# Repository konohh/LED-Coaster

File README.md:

# LED-Coaster
Enlight your beverage

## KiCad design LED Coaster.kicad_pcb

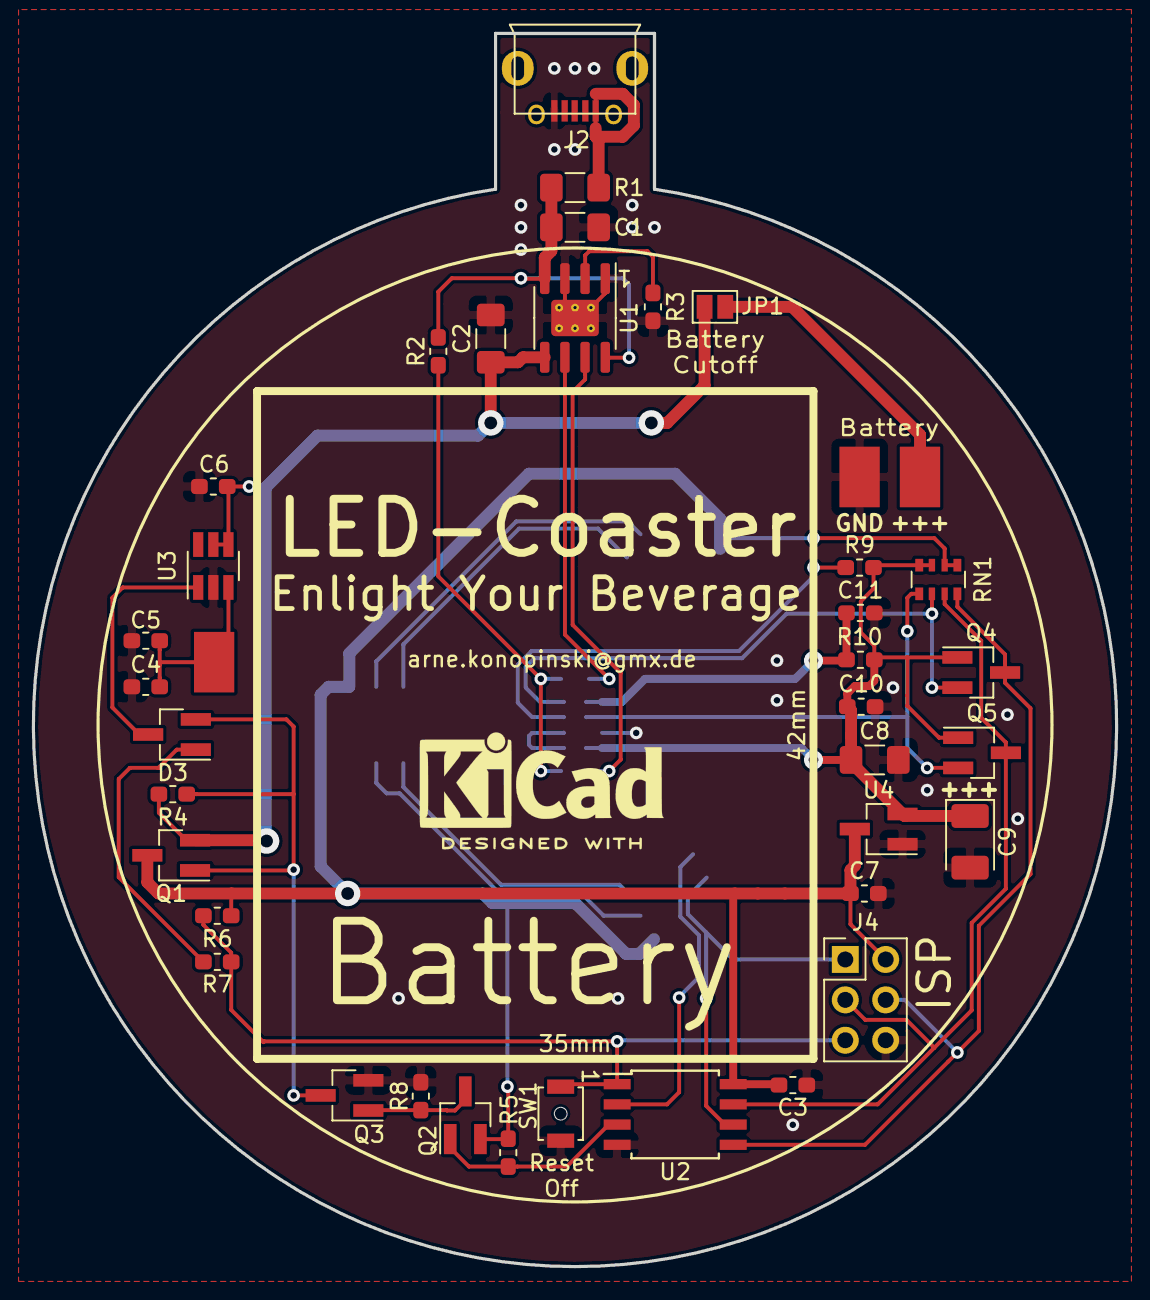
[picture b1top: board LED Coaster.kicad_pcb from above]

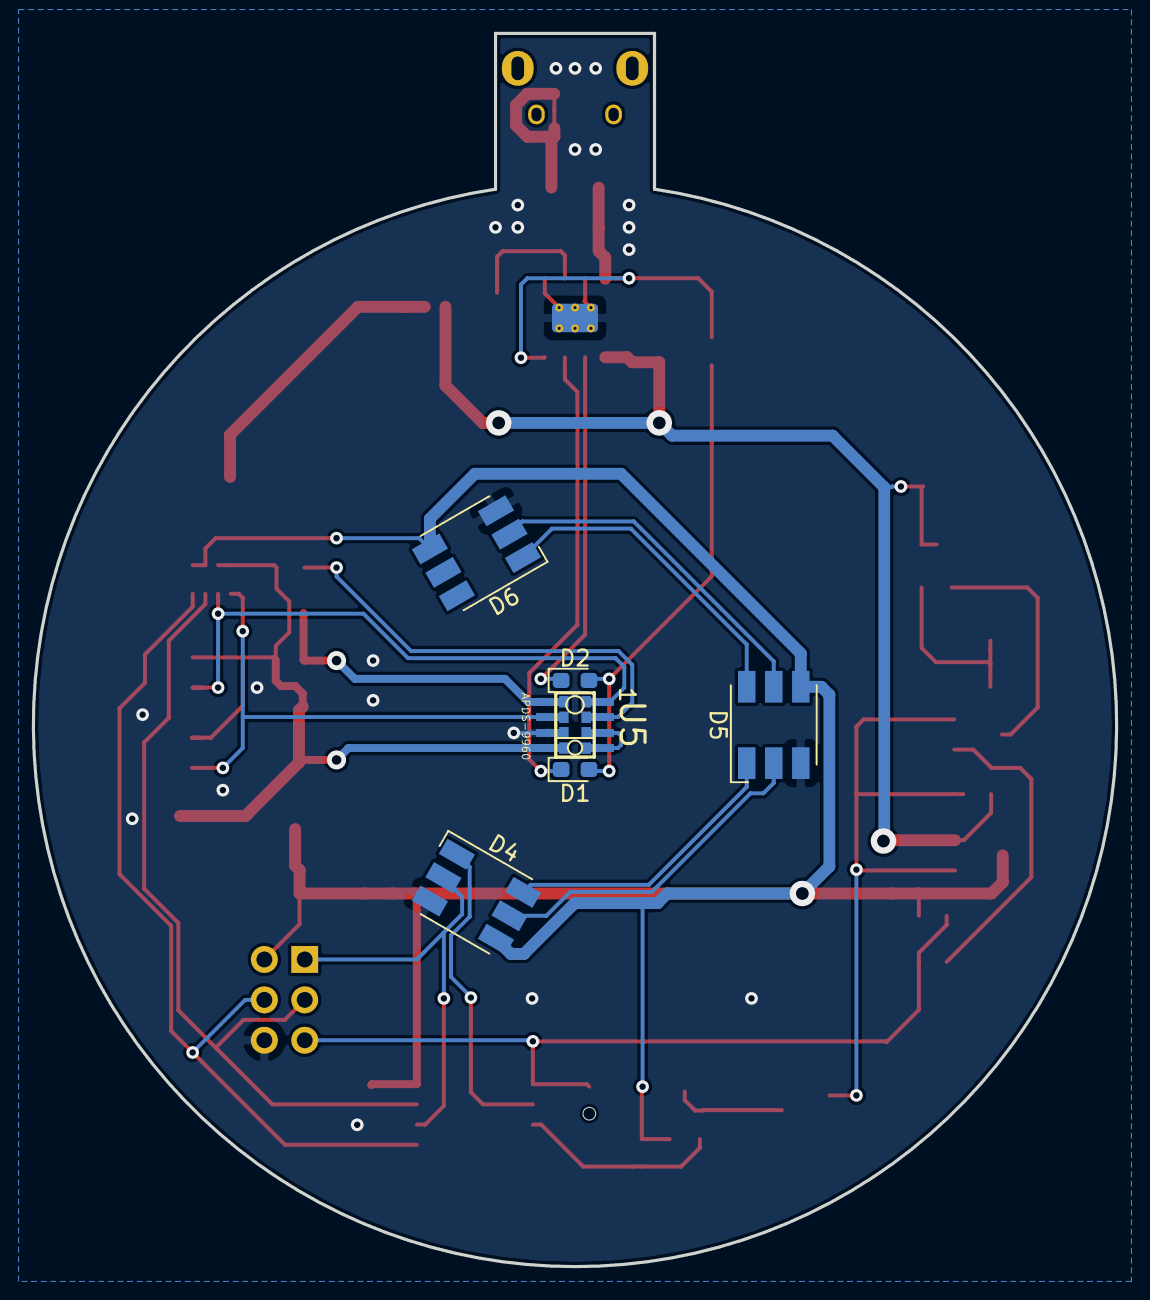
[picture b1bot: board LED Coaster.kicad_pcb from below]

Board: 2 copper layers, 68.1 x 77.6 mm, 45 parts (6 on the bottom side), 31 nets.

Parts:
C1, C2, C8: 10; C_1206_3216Metric_Pad1.42x1.75mm_HandSolder
C3, C6: .1; C_0603_1608Metric_Pad1.05x0.95mm_HandSolder
C4, C5: 33pF; C_0603_1608Metric_Pad1.05x0.95mm_HandSolder
C7, C10, C11: 1; C_0603_1608Metric_Pad1.05x0.95mm_HandSolder
C9: 47; CP_EIA-3528-15_AVX-H_Pad1.50x2.35mm_HandSolder
D1: Red; LED_0603_1608Metric_Pad1.05x0.95mm_HandSolder
D2: Green; LED_0603_1608Metric_Pad1.05x0.95mm_HandSolder
D3: BAV70; SOT-23_Handsoldering
D4, D5, D6: APA102; LED_RGB_5050-6
J1: Battery Positiv; SolderPad-100x150
J2: USB_B_Micro; USB_Micro-B_XKB_Enterprise_U254-051T-4BH23-S2B
J3: Battery GND; SolderPad-100x150
J4: ISP; PinHeader_2x03_P2.54mm_Vertical
J5: TouchPad; SolderPad-100x150
JP1: Battery Cutoff; SolderJumper-2_P1.3mm_Open_Pad1.0x1.5mm
Q1: IRLML6401; SOT-23_Handsoldering
Q2: BSS84; SOT-23_Handsoldering
Q3, Q4, Q5: BSS123; SOT-23_Handsoldering
R1: 0R4; R_1206_3216Metric_Pad1.42x1.75mm_HandSolder
R2: 1k; R_0603_1608Metric_Pad1.05x0.95mm_HandSolder
R3: 4k7; R_0603_1608Metric_Pad1.05x0.95mm_HandSolder
R4, R5, R8: 220k; R_0603_1608Metric_Pad1.05x0.95mm_HandSolder
R6: 2k2; R_0603_1608Metric_Pad1.05x0.95mm_HandSolder
R7, R9: 22k; R_0603_1608Metric_Pad1.05x0.95mm_HandSolder
R10: 22R; R_0603_1608Metric_Pad1.05x0.95mm_HandSolder
RN1: 4x10k; R_Array_Convex_4x0603
SW1: Reset / OFF; SW_SPST_B3U-1000P-B
U1: TP4056; SOIC-8-1EP_3.9x4.9mm_P1.27mm_EP2.29x3mm_ThermalVias
U2: ATtiny85-x0SU; SOIJ-8_5.3x5.3mm_P1.27mm
U3: TTP223-BA6; SOT-23-6_Handsoldering
U4: MCP1700-3302; SOT-23_Handsoldering
U5: APDS-9960; APDS-9960-Handsolder

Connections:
+3V3: C8.1, C9.1, C10.1, Q4.1, Q5.1, R9.2, R10.2, RN1.3, RN1.4, U4.2, U5.5
+BATT: C2.1, C6.1, JP1.1, Q1.2, R4.2, U1.5, U3.4, U3.5
/LED_Clock: D4.2, J4.1, U2.6
/LED_Data: D4.1, U2.2
/MODE: J4.5, R6.1, R7.1, SW1.1, U2.1
/OFF: Q2.1, R5.1, U2.3
/SCL_HV: J4.3, Q5.3, RN1.7, U2.7
/SCL_LV: Q5.2, RN1.5, U5.7
/SDA_HV: J4.4, Q4.3, RN1.8, U2.5
/SDA_LV: Q4.2, RN1.6, U5.1
GND: C1.2, C2.2, C3.2, C4.2, C5.2, C6.2, C7.2, C8.2, C9.2, C10.2, C11.2, D4.3, D5.3, D6.3, J2.5, J3.1, J4.6, Q3.2, R3.2, R8.1, SW1.2, U1.1, U1.3, U1.9, U2.4, U3.2, U4.1, U5.6
unnamed: C1.1, R1.1, R2.1, U1.4, U1.8
unnamed: C4.1, C5.1, J5.1, U3.3
unnamed: C11.1, R10.1, U5.8
unnamed: D1.1, U1.7
unnamed: D1.2, D2.2, R2.2
unnamed: D2.1, U1.6
unnamed: D3.1, R7.2
unnamed: D3.2, Q1.1, Q3.3, R4.1
unnamed: D3.3, U3.1
unnamed: D4.5, D5.2
unnamed: D4.6, D5.1
unnamed: D5.5, D6.2
unnamed: D5.6, D6.1
unnamed: J1.1, JP1.2
unnamed: J2.1, R1.2
unnamed: Q2.3, Q3.1, R8.2
unnamed: R3.1, U1.2
unnamed: R9.1, U5.2
unnamed: U5.3, U5.4
VDD: C3.1, C7.1, D4.4, D5.4, D6.4, J4.2, Q1.3, Q2.2, R5.2, R6.2, RN1.1, RN1.2, U2.8, U4.3
